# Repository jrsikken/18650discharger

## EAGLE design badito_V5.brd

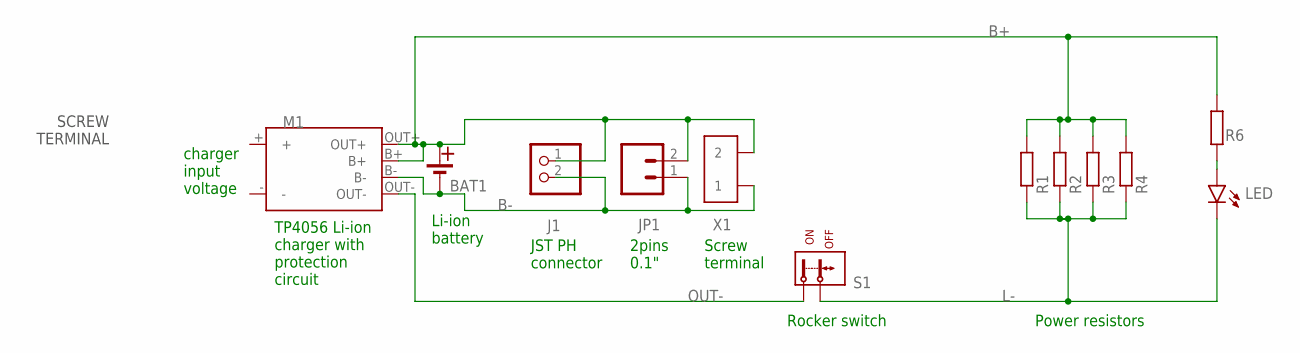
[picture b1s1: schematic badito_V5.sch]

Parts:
BAT1: KS18650X1-SMT
J1: JST_2PIN-SMT; JST-PH-2-SMT
JP1: 1X02_2.54MM_ROUND
LED: RED; LED-0603
M1: TP4056_CHG_PROT; BAT_CHG_PROT_BRD_27.9X17.4MM
R1, R2, R3, R4: R; R_PWR_CEMENT_10W
R6: 250R; R0603
S1: SWITCH_ROCKER_KCDI-101
X1: ED350/2

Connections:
B+: BAT1.+, J1.1 (2), JP1.2, M1.B+, M1.OUT+, R1.1 (2), R2.1 (2), R3.1 (2), R4.1 (2), R6.2, X1.P$2 (2)
B-: BAT1.-, J1.2 (1), JP1.1, M1.B-, X1.P$1 (1)
L-: LED.C, R1.2 (1), R2.2 (1), R3.2 (1), R4.2 (1), S1.2 (2.1), S1.2_2 (2.1)
unnamed: LED.A, R6.1
OUT-: M1.OUT-, S1.1 (1.1), S1.1_1 (1.1)

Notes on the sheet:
SCREW TERMINAL
TP4056 Li-ion charger with protection circuit
Rocker switch
Power resistors
Li-ion battery
JST PH connector
Screw terminal
2pins 0.1"
charger input voltage

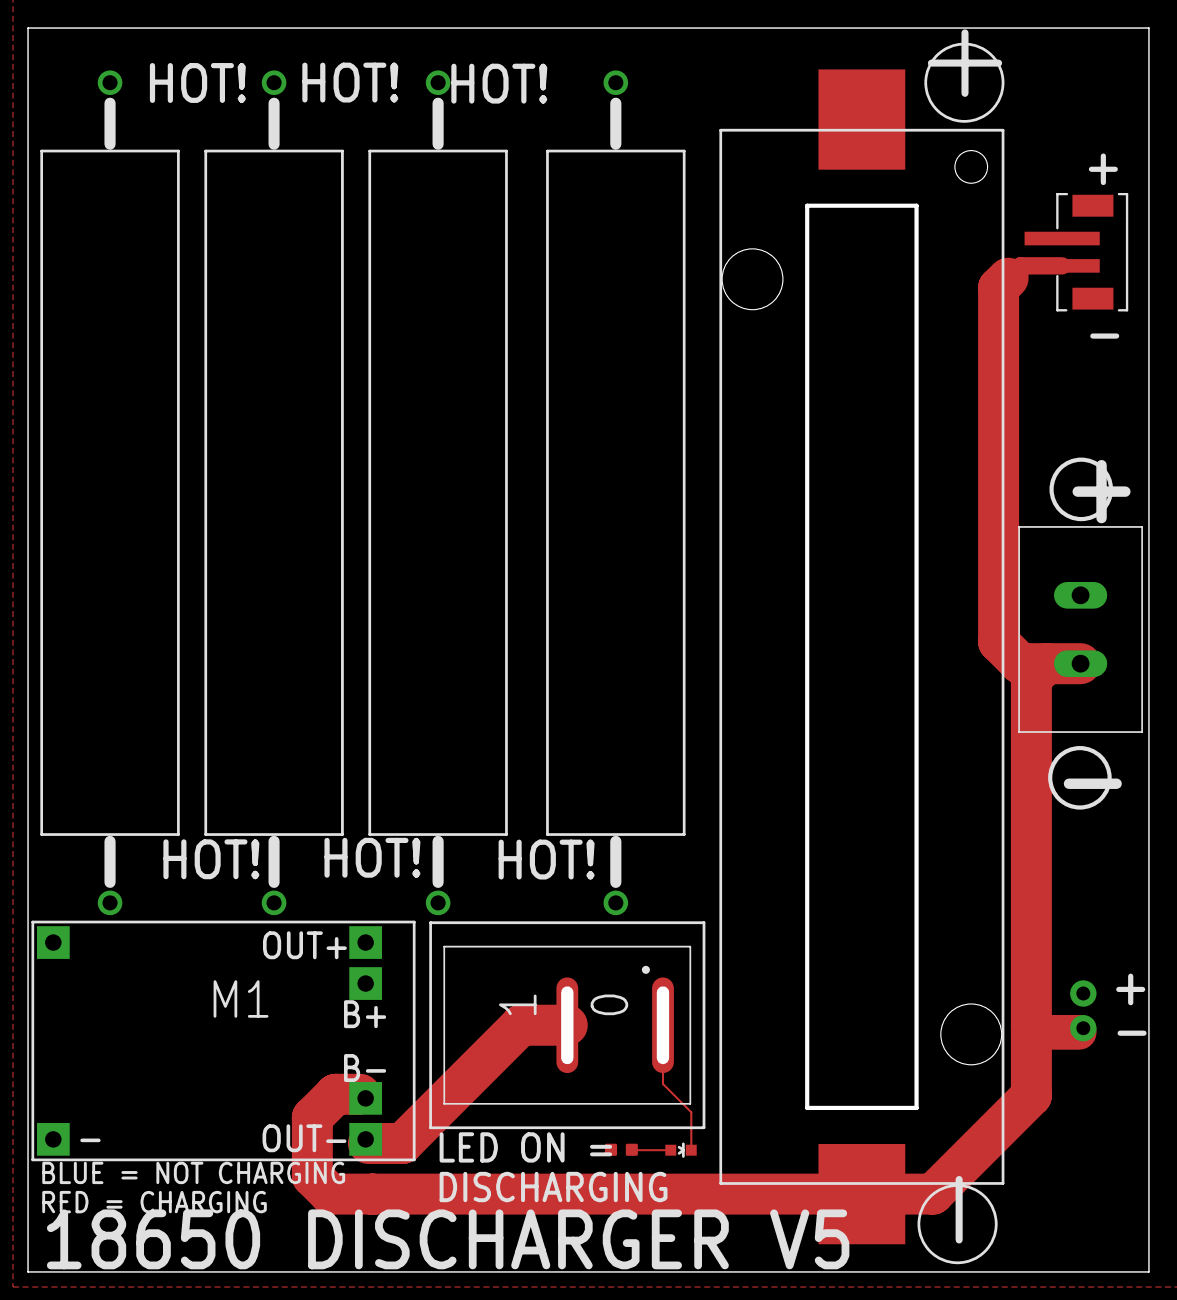
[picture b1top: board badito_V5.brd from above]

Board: 2 copper layers, 82.0 x 91.0 mm, 12 parts (0 on the bottom side), 5 nets.

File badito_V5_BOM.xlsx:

reference designator | Description |  | order EUR | order qty | order each | qty | shipping | shipping per unit | cost | stock | ordered
J1 | connector JST PH | https://www.aliexpress.com/item/4000036823994.html | 1.87 | 200 | 9.3500000000000007E-3 | 1 | 1.44 | 7.1999999999999998E-3 | 1.6550000000000002E-2 | 120 | 0
R1, R2, R3, R4 | resistor power | https://www.aliexpress.com/item/1921263979.html | 0.49 | 10 | 4.9000000000000002E-2 | 4 | 1.9 | 0.76 | 0.95599999999999996 | 19 | 10
LED | LED red 0603 | https://www.aliexpress.com/item/32947001269.html | 0.38 | 100 | 3.8E-3 | 1 | 1.07 | 1.0700000000000001E-2 | 1.4500000000000001E-2 | 0 | 100
X1 | terminal block 5.0mm P128-2p | https://www.aliexpress.com/item/32843866688.html | 1.44 | 20 | 7.1999999999999995E-2 | 1 | 2.94 | 0.14699999999999999 | 0.21899999999999997 | 5 | 20
BAT1 | battery holder | https://www.aliexpress.com/item/4001152338150.html | 0.28000000000000003 | 1 | 0.28000000000000003 | 1 | 1.0900000000000001 | 1.0900000000000001 | 1.37 | 4 | 6
M1 | TP4056 charger protected | https://www.aliexpress.com/item/1005001567784022.html | 1.74 | 10 | 0.17399999999999999 | 1 | 1.0900000000000001 | 0.10900000000000001 | 0.28300000000000003 | 20 | 0
S1 | rocker switch | https://www.aliexpress.com/item/32990004998.html | 0.35 | 10 | 3.4999999999999996E-2 | 1 | 1.78 | 0.17799999999999999 | 0.21299999999999999 | 8 | 10
PCB | PCB | https://jlcpcb.com/ | 4.1500000000000004 | 10 | 0.41500000000000004 | 1 | 10.91 | 1.091 | 1.506 | 3 | 10
n/a | rubber feet | https://www.aliexpress.com/item/32962698458.html | 1.63 | 40 | 4.0749999999999995E-2 | 4 | 0.28999999999999998 | 2.8999999999999998E-2 | 0.19199999999999998 | 30 | 40
 |  |  |  |  |  | total euro |  |  | 4.7700500000000003
